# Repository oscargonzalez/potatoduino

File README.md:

# potatoduino
Arduino based Pomodoro Timer
Oscar Gonzalez - November 2017

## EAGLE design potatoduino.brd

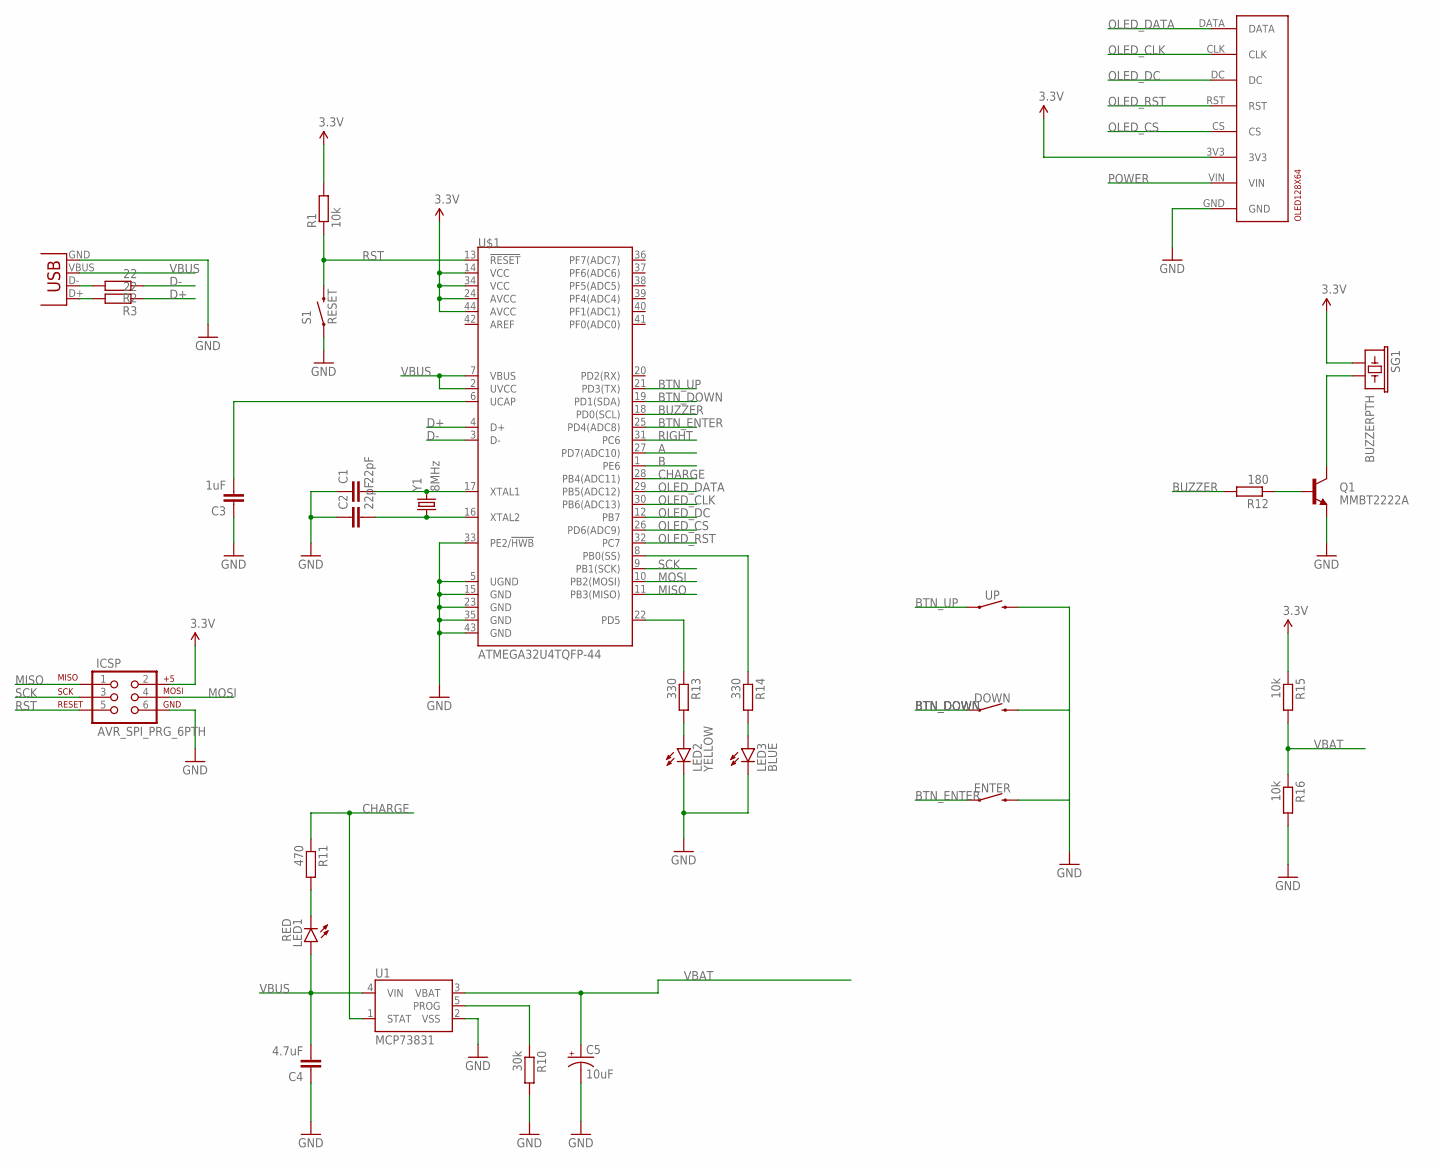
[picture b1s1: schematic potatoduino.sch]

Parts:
C1, C2: 22pF; 1206
C3: 1uF; 1206
C4: 4.7uF; 1206
C5: 10uF; EIA3216
DOWN: MOMENTARY-SWITCH-SPST-PTH-12MM; TACTILE_SWITCH_PTH_12MM
ENTER: MOMENTARY-SWITCH-SPST-PTH-12MM; TACTILE_SWITCH_PTH_12MM
ICSP: AVR_SPI_PRG_6PTH; 2X3
JP1: USB-SMD-NS; USB-MINIB-NOSTOP
LED1: RED; LED-0603
LED2: YELLOW; LED-0603
LED3: BLUE; LED-0603
OLED128X64: OLED128X64-ADAFRUIT938; 938
Q1: MMBT2222A; SOT23-3
R1, R15, R16: 10k; M0805
R2, R3: 22; M0805
R10: 30k; M0805
R11: 470; M0805
R12: 180; M0805
R13, R14: 330; M0805
S1: RESET; TACTILE-SWITCH-SMD
SG1: BUZZERPTH; BUZZER-12MM
U1: MCP73831; SOT23-5
U$1: ATMEGA32U4TQFP-44; TQFP44
UP: MOMENTARY-SWITCH-SPST-PTH-12MM; TACTILE_SWITCH_PTH_12MM
Y1: 8MHz; HC49US

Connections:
3.3V: ICSP.2, OLED128X64.3V3, R1.2, R15.1, SG1.+ (1), U$1.14 (VCC), U$1.24 (AVCC), U$1.34 (VCC), U$1.44 (AVCC)
A: U$1.27 (PD7(ADC10))
B: U$1.1 (PE6)
BTN_DOWN: DOWN.1, U$1.19 (PD1(SDA))
BTN_ENTER: ENTER.1, U$1.25 (PD4(ADC8))
BTN_UP: U$1.21 (PD3(TX)), UP.1
BUZZER: R12.2, U$1.18 (PD0(SCL))
CHARGE: R11.1, U1.1 (STAT), U$1.28 (PB4(ADC11))
D+: R3.1, U$1.4 (D+)
D-: R2.1, U$1.3 (D-)
GND: C1.1, C2.1, C3.1, C4.1, C5.C (-), DOWN.3 (2), ENTER.3 (2), ICSP.6, JP1.GND, LED2.C, LED3.C, OLED128X64.GND, Q1.2 (E), R10.2, R16.2, S1.1, U1.2 (VSS), U$1.5 (UGND), U$1.15 (GND), U$1.23 (GND), U$1.33 (PE2/!HWB), U$1.35 (GND), U$1.43 (GND), UP.3 (2)
MISO: ICSP.1, U$1.11 (PB3(MISO))
MOSI: ICSP.4, U$1.10 (PB2(MOSI))
unnamed: C1.2, U$1.17 (XTAL1), Y1.2
unnamed: C2.2, U$1.16 (XTAL2), Y1.1
unnamed: Q1.3 (C), SG1.- (2)
unnamed: JP1.D-, R2.2
unnamed: JP1.D+, R3.2
unnamed: C3.2, U$1.6 (UCAP)
unnamed: R10.1, U1.5 (PROG)
unnamed: LED1.C, R11.2
unnamed: Q1.1 (B), R12.1
unnamed: LED2.A, R13.2
unnamed: LED3.A, R14.2
unnamed: R13.1, U$1.22 (PD5)
unnamed: R14.1, U$1.8 (PB0(SS))
OLED_CLK: OLED128X64.CLK, U$1.30 (PB6(ADC13))
OLED_CS: OLED128X64.CS, U$1.26 (PD6(ADC9))
OLED_DATA: OLED128X64.DATA, U$1.29 (PB5(ADC12))
OLED_DC: OLED128X64.DC, U$1.12 (PB7)
OLED_RST: OLED128X64.RST, U$1.32 (PC7)
POWER: OLED128X64.VIN
RIGHT: U$1.31 (PC6)
RST: ICSP.5, R1.1, S1.3 (2), U$1.13 (!RESET)
SCK: ICSP.3, U$1.9 (PB1(SCK))
VBAT: C5.A (+), R15.2, R16.1, U1.3 (VBAT)
VBUS: C4.2, JP1.VBUS, LED1.A, U1.4 (VIN), U$1.2 (UVCC), U$1.7 (VBUS)

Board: 2 copper layers, 34 parts (22 on the bottom side), 33 nets, no tracks yet.

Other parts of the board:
U$2, U$4, U$5, U$6: STAND-OFF

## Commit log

2017-11-22 First!
2017-11-25 added src of the prototype

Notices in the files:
parts and their libraries:
SparkFun-Electromechanical: Licensing: Creative Commons ShareAlike 4.0 International - https://creativecommons.org/licenses/by-sa/4.0
